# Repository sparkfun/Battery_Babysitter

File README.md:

SparkFun Battery Babysitter
========================================

[*SparkFun Battery Babysitter (PRT-13777)*](https://www.sparkfun.com/products/13777)

The [SparkFun Battery Babysitter](https://www.sparkfun.com/products/13777) is an all-in-one single-cell lithium polymer (LiPo) battery manager. It’s half **battery-charger**, half **battery monitor**, and it’s all you’ll ever need to keep your battery-powered project running safely and extensively.

The Battery Babysitter features a pair of Texas Instruments LiPo-management IC’s: a [BQ24075 battery charger](http://www.ti.com/product/BQ24075) and a [BQ27441-G1A fuel gauge](http://www.ti.com/product/BQ27441-G1). The BQ24075 supports adjustable charge rates up to 1.5A, as well as USB-compliant 100mA and 500mA options. It also features power-path management, guaranteeing reliable power to your project.

The self-calibrating, I2C-based BQ27441-G1A measures your battery’s voltage to estimate its charge percentage and remaining capacity. The chip is also hooked up to a current-sensing resistor, which allows it to measure current and power! It’s a handy IC to have, especially if you ever need to keep an extra eye on your project’s power draw.

Repository Contents
-------------------

* **/Documentation** - Data sheets, additional product information
* **/Hardware** - Eagle design files (.brd, .sch)
* **/Libraries** - Libraries for use with the Battery Babysitter
* **/Production** - Production panel files (.brd)

Documentation
--------------
* **[BQ27441 LiPo Fuel Gauge Arduino Library](https://github.com/sparkfun/SparkFun_BQ27441_Arduino_Library)** - Arduino library for the Battery Babysitter's BQ27441-G1A LiPo Fuel Gauge.
* **[Hookup Guide](https://learn.sparkfun.com/tutorials/battery-babysitter-hookup-guide)** - Basic hookup guide for the Battery Babysitter.
* **[SparkFun Fritzing repo](https://github.com/sparkfun/Fritzing_Parts)** - Fritzing diagrams for SparkFun products.
* **[SparkFun 3D Model repo](https://github.com/sparkfun/3D_Models)** - 3D models of SparkFun products. 
* **[SparkFun Graphical Datasheets](https://github.com/sparkfun/Graphical_Datasheets)** -Graphical Datasheets for various SparkFun products.

Product Versions
----------------
* [Battery Babysitter v1.0 (PRT-13777)](https://www.sparkfun.com/products/13777)- Initial release of the SparkFun Battery Babysitter.

Version History
---------------
* [1.0](https://github.com/sparkfun/Battery_Babysitter/releases/tag/V_1.0) - v1.0 Hardware release

License Information
-------------------

This product is _**open source**_! 

Please review the LICENSE.md file for license information. 

If you have any questions or concerns on licensing, please contact techsupport@sparkfun.com.

Distributed as-is; no warranty is given.

- Your friends at SparkFun.

_<COLLABORATION CREDIT>_

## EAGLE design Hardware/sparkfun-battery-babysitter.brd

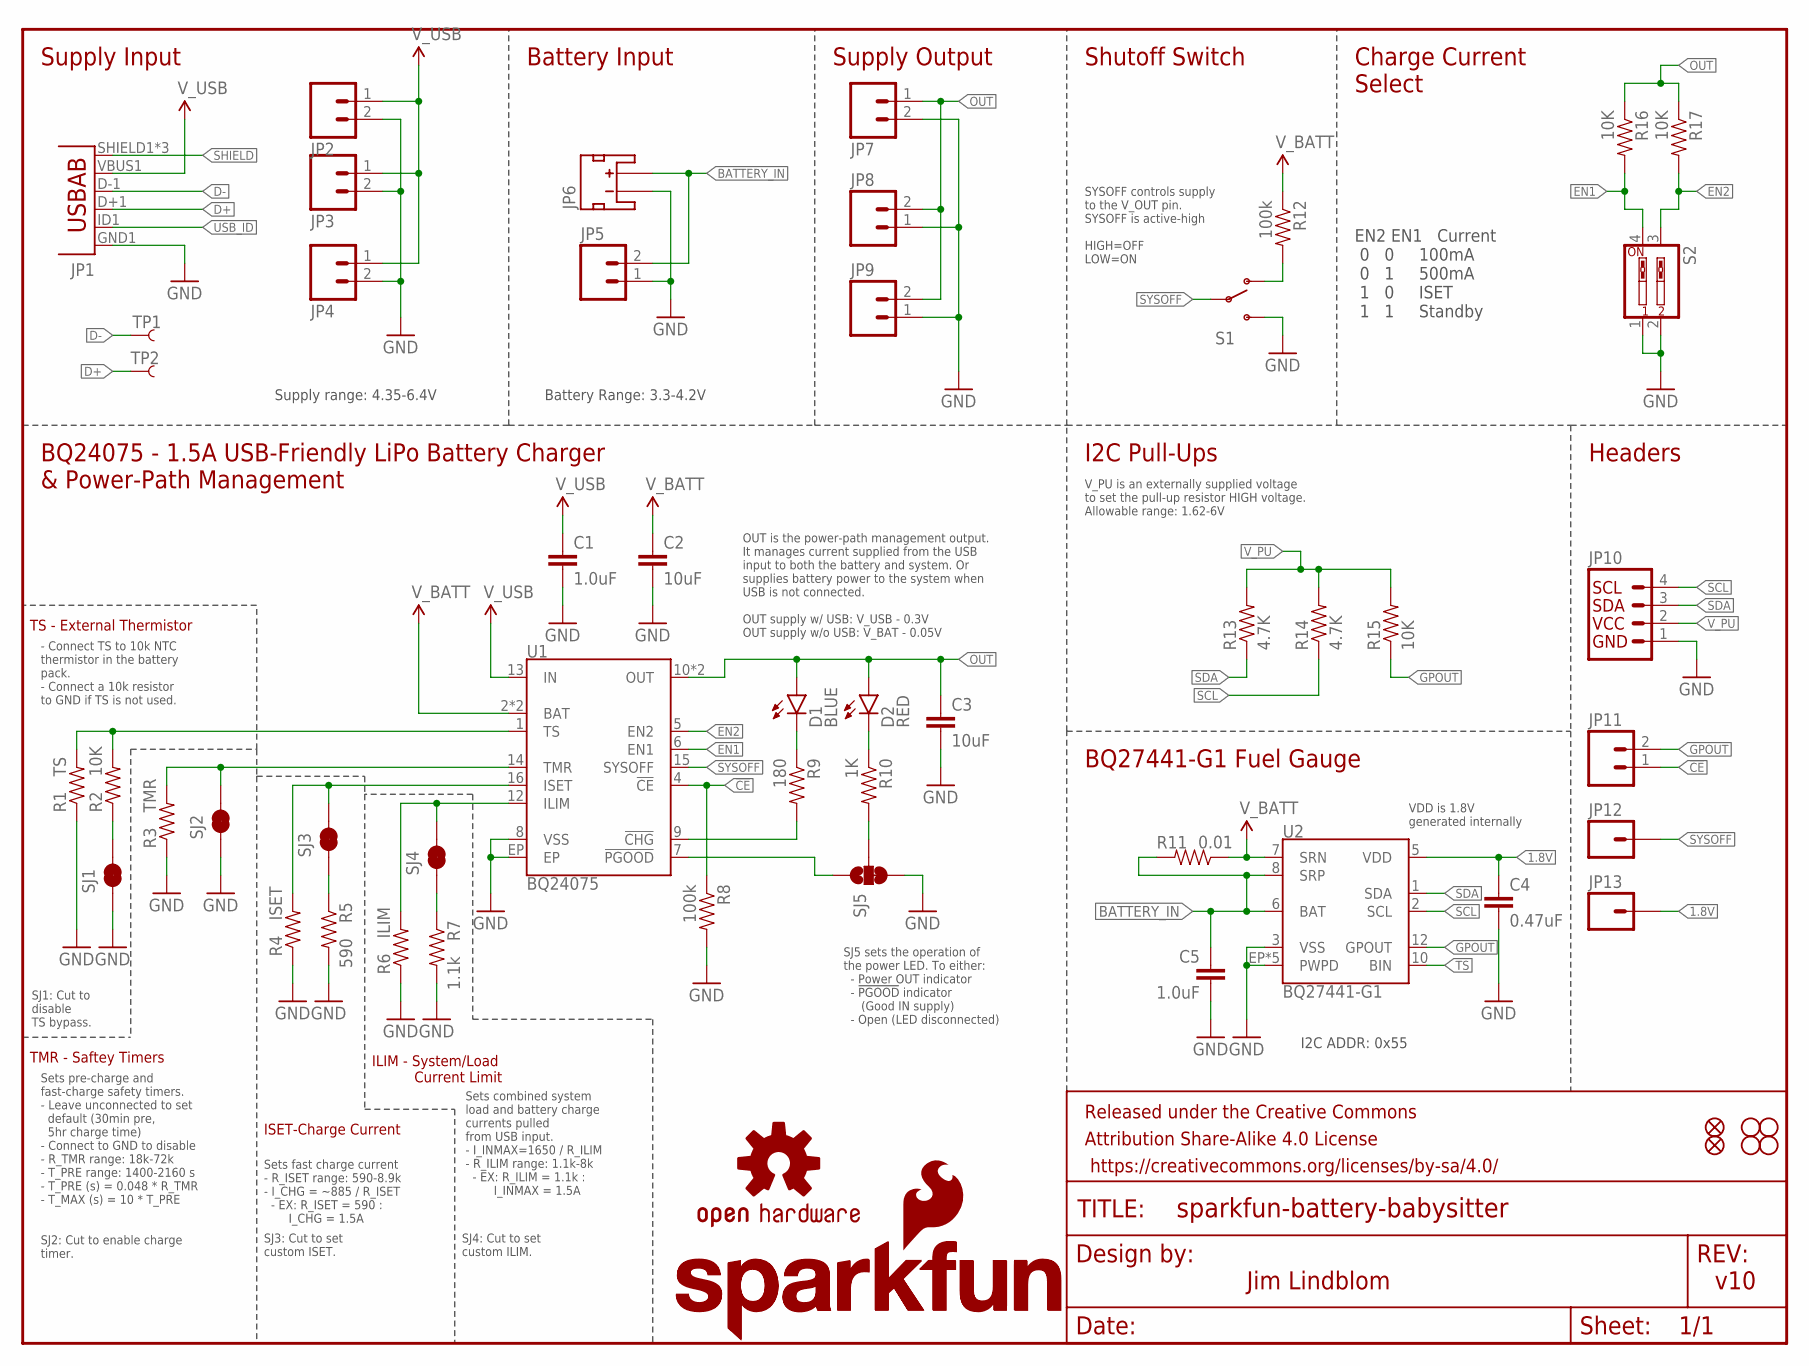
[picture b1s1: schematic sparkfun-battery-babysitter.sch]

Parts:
C1: 1.0uF; 1206-CAP
C2, C3: 10uF; 0805-CAP
C4: 0.47uF; 0603-CAP
C5: 1.0uF; 0603-CAP
D1: BLUE; LED-0603
D2: RED; LED-0603
FID1, FID2: FIDUCIAL1X2; FIDUCIAL-1X2
FRAME1: FRAME-LETTER; CREATIVE_COMMONS
JP1: USB-ABCONN-11794; USB-AB-MICRO-SMD_V03
JP2, JP4, JP5, JP8, JP11: M021X02_NO_SILK; 1X02_NO_SILK
JP3, JP7: M023.5MM-NO_SILK; SCREWTERMINAL-3.5MM-2-NS
JP6: JST_2MM_MALE; JST-2-SMD
JP9: M02-JST-2-PTH-NO_SILK; JST-2-PTH-NS
JP10: I2C_STANDARD_NO_SILK; 1X04_NO_SILK
JP12, JP13: M01PTH_NO_SILK_YES_STOP; 1X01_NO_SILK
LOGO1: SFE_LOGO_NAME.1_INCH; SFE_LOGO_NAME_.1
LOGO2: SFE_LOGO_NAME_FLAME.1_INCH; SFE_LOGO_NAME_FLAME_.1
LOGO3: OSHW-LOGOS; OSHW-LOGO-S
R1: TS; 1/6W-RES
R2, R15, R16, R17: 10K; 0603-RES
R3: TMR; 1/6W-RES
R4: ISET; 1/6W-RES
R5: 590; 0603-RES
R6: ILIM; 1/6W-RES
R7: 1.1k; 0603-RES
R8, R12: 100k; 0603-RES
R9: 180; 0603-RES
R10: 1K; 0603-RES
R11: 0.01; 1206
R13, R14: 4.7K; 0603-RES
S1: SWITCH-SPDT-SMD-A; SWITCH-SPST-SMD-A
S2: SW_DIP-2-SMT-HALFSIZE; DIPSWITCH-02-50MIL
SJ1, SJ2, SJ3, SJ4: JUMPER-PAD-2-NC_BY_TRACE; PAD-JUMPER-2-NC_BY_TRACE_YES_SILK
SJ5: JUMPER-PAD-3-2OF3_NC_BY_TRACE_SMALL; PAD-JUMPER-3-2OF3_NC_BY_TRACE_YES_SILK_FULL_BOX
STANDOFF1, STANDOFF2, STANDOFF3, STANDOFF4: STAND-OFF
TP1, TP2: TEST-POINT3X4; PAD.03X.04
U1: BQ24075; PVQFN-N16
U2: BQ27441-G1; PDSO-N12

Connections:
1.8V: C4.1, JP13.1, U2.5 (VDD)
!CE!: JP11.1, R8.1, U1.4 (!CE!)
!CHG!: R9.2, U1.9 (!CHG!)
!PGOOD!: SJ5.1, U1.7 (!PGOOD!)
BATTERY_IN: C5.1, JP5.2, JP6.2 (+), R11.2, U2.6 (BAT), U2.8 (SRP)
D+: JP1.D+1 (D+), TP2.P$1
D-: JP1.D-1 (D-), TP1.P$1
EN1: R16.2, S2.4, U1.6 (EN1)
EN2: R17.2, S2.3, U1.5 (EN2)
GND: C1.2, C2.2, C3.2, C4.2, C5.2, JP1.GND1 (GND), JP2.2, JP3.2, JP4.2, JP5.1, JP6.1 (-), JP7.2, JP8.1, JP9.1, JP10.1, R1.1, R3.1, R4.1, R5.2, R6.1, R7.2, R8.2, S1.3 (S), S2.1, S2.2, SJ1.1, SJ2.1, SJ5.3, U1.8 (VSS), U1.EP, U2.3 (VSS), U2.EP (PWPD), U2.EP1 (PWPD), U2.EP2 (PWPD), U2.EP3 (PWPD), U2.EP4 (PWPD)
GPOUT: JP11.2, R15.1, U2.12 (GPOUT)
ILIM: R6.2, SJ4.2, U1.12 (ILIM)
ISET: R4.2, SJ3.2, U1.16 (ISET)
unnamed: R2.1, SJ1.2
unnamed: R7.1, SJ4.1
unnamed: R5.1, SJ3.1
unnamed: R12.2, S1.1 (O)
unnamed: R10.2, SJ5.2
unnamed: D1.C, R9.1
unnamed: D2.C, R10.1
OUT: C3.1, D1.A, D2.A, JP7.1, JP8.2, JP9.2, R16.1, R17.1, U1.10 (OUT), U1.11 (OUT)
SCL: JP10.4, R14.1, U2.2 (SCL)
SDA: JP10.3, R13.1, U2.1 (SDA)
SHIELD: JP1.SHIELD1 (SHIELD), JP1.SHIELD2 (SHIELD), JP1.SHIELD3 (SHIELD)
SYSOFF: JP12.1, S1.2, U1.15 (SYSOFF)
TMR: R3.2, SJ2.2, U1.14 (TMR)
TS: R1.2, R2.2, U1.1 (TS), U2.10 (BIN)
USB_ID: JP1.ID1 (USBID)
V_BATT: C2.1, R11.1, R12.1, U1.2 (BAT), U1.3 (BAT), U2.7 (SRN)
V_PU: JP10.2, R13.2, R14.2, R15.2
V_USB: C1.1, JP1.VBUS1 (VBUS), JP2.1, JP3.1, JP4.1, U1.13 (IN)

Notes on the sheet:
EN2 EN1 Current 0 0 100mA 0 1 500mA 1 0 ISET 1 1 Standby
Sets fast charge current - R_ISET range: 590-8.9k - I_CHG = ~885 / R_ISET - EX: R_ISET = 590 : I_CHG = 1.5A
Sets combined system load and battery charge currents pulled from USB input. - I_INMAX=1650 / R_ILIM - R_ILIM range: 1.1k-8k - EX: R_ILIM = 1.1k : I_INMAX = 1.5A
Supply Input
Battery Input
Supply Output
Shutoff Switch
Charge Current Select
BQ24075 - 1.5A USB-Friendly LiPo Battery Charger & Power-Path Management
I2C Pull-Ups
BQ27441-G1 Fuel Gauge
Headers
Jim Lindblom
v10
SYSOFF controls supply to the V_OUT pin. SYSOFF is active-high HIGH=OFF LOW=ON
SJ1: Cut to disable TS bypass.
SJ3: Cut to set custom ISET.
SJ4: Cut to set custom ILIM.
ILIM - System/Load Current Limit
ISET-Charge Current
TMR - Saftey Timers
Sets pre-charge and fast-charge safety timers. - Leave unconnected to set default (30min pre, 5hr charge time) - Connect to GND to disable - R_TMR range: 18k-72k - T_PRE range: 1400-2160 s - T_PRE (s) = 0.048 * R_TMR - T_MAX (s) = 10 * T_PRE
SJ2: Cut to enable charge timer.
TS - External Thermistor
- Connect TS to 10k NTC thermistor in the battery pack. - Connect a 10k resistor to GND if TS is not used.
V_PU is an externally supplied voltage to set the pull-up resistor HIGH voltage. Allowable range: 1.62-6V
Supply range: 4.35-6.4V
VDD is 1.8V generated internally
OUT is the power-path management output. It manages current supplied from the USB input to both the battery and system. Or supplies battery power to the system when USB is not connected. OUT supply w/ USB: V_USB - 0.3V OUT supply w/o USB: V_BAT - 0.05V
I2C ADDR: 0x55
SJ5 sets the operation of the power LED. To either: - Power OUT indicator - !PGOOD! indicator (Good IN supply) - Open (LED disconnected)
Battery Range: 3.3-4.2V

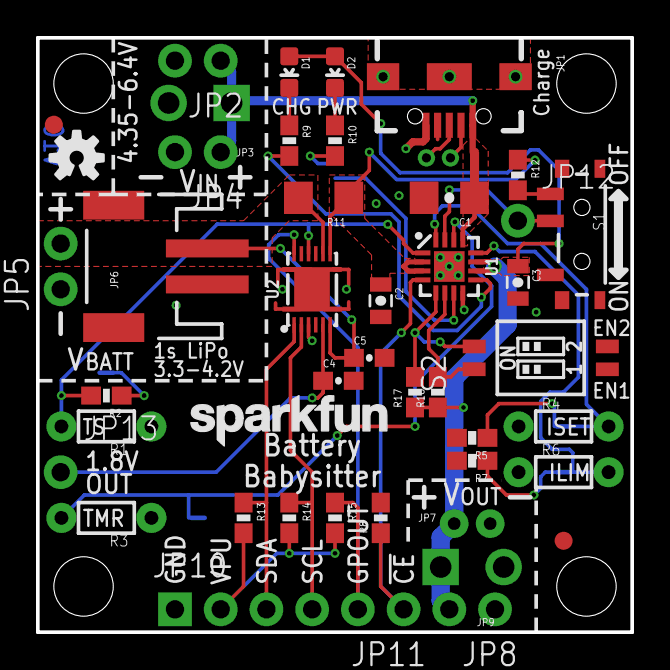
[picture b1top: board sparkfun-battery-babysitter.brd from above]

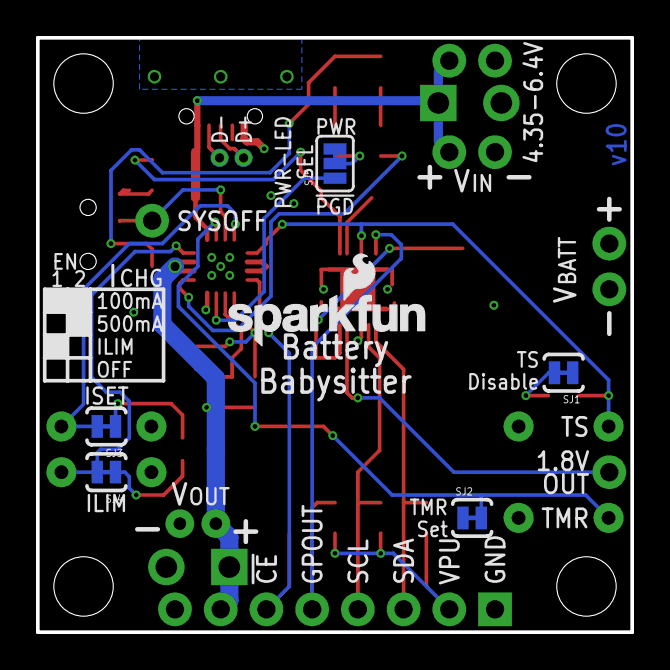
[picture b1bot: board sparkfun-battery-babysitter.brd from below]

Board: 2 copper layers, 33.0 x 33.0 mm, 58 parts (8 on the bottom side), 30 nets.

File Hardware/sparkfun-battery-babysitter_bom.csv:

Comment,Designator,Footprint,LCSC Part #
,JP12,1X01_NO_SILK,
,JP13,1X01_NO_SILK,
,JP2,1X02_NO_SILK,
,JP4,1X02_NO_SILK,
,JP5,1X02_NO_SILK,
,JP8,1X02_NO_SILK,
,JP11,1X02_NO_SILK,
,JP10,1X04_NO_SILK,
,JP9,JST-2-PTH-NS,
,JP6,JST-2-SMD,
,SJ1,PAD-JUMPER-2-NC_BY_TRACE_YES_SILK,
,SJ2,PAD-JUMPER-2-NC_BY_TRACE_YES_SILK,
,SJ3,PAD-JUMPER-2-NC_BY_TRACE_YES_SILK,
,SJ4,PAD-JUMPER-2-NC_BY_TRACE_YES_SILK,
,SJ5,PAD-JUMPER-3-2OF3_NC_BY_TRACE_YES_SILK_FULL_BOX,
,TP1,PAD.03X.04,
,TP2,PAD.03X.04,
,JP3,SCREWTERMINAL-3.5MM-2-NS,
,JP7,SCREWTERMINAL-3.5MM-2-NS,
0.01,R11,1206,
0.47uF,C4,0603-CAP,
1.0uF,C5,0603-CAP,
1.0uF,C1,1206-CAP,
1.1k,R7,0603-RES,
1K,R10,0603-RES,
4.7K,R13 R14,0603-RES,
10K,R2 R15 R16 R17,0603-RES,
10uF,C2 C3,0805-CAP,
100k,R8 R12,0603-RES,
180,R9,0603-RES,
590,R5,0603-RES,
BLUE,D1,LED-0603,
BQ24075,U1,PVQFN-N16,
BQ27441-G1,U2,PDSO-N12,
FIDUCIAL1X2,FID1 FID2,FIDUCIAL-1X2,
ILIM,R6,1/6W-RES,
ISET,R4,1/6W-RES,
RED,D2,LED-0603,
RIGHT_ANGLE_SLIDE_SWITCH_SMD,S1,SWITCH-SPST-SMD-A,
SW_DIP-2_SMD,S2,DIPSWITCH-02-50MIL,
TMR,R3,1/6W-RES,
TS,R1,1/6W-RES,
USB-AB-MICRO-SMD_V03,JP1,USB-AB-MICRO-SMD_V03,

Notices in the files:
parts and their libraries:
SparkFun-Aesthetics: Licensing: Creative Commons ShareAlike 4.0 International - https://creativecommons.org/licenses/by-sa/4.0
SparkFun-Aesthetics: Released under the Creative Commons Attribution Share-Alike 4.0 License
SparkFun-Aesthetics: https://creativecommons.org/licenses/by-sa/4.0
